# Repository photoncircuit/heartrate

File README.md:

# Heart Rate Monitoring System
Bachelors degree final project: portable heart rate monitoring system with bluetooth data transfer capability

The aim of this project is to design and construct a functional heart rate monitoring system. The device will amplify pulse measurements taken from an individual’s fingertip. The system is based on an active band pass filter which will amplify a selected signal frequency while attenuating noise and interference. Signals acquired from the fingertip sensor will be analogue and require conversion to digital. The use of an analogue to digital convertor (ADC) is employed in order for the microcontroller to process the information taken from the individual. After processing, the microcontroller will display pulse rate data on an LCD display and transmit the information wirelessly through the use of the Bluetooth communication protocol. It enables the user to move the device to any area desirable within their homes. A user can then view the transmitted data on an application, using a graphical user interface, running on their personal computers. Implementing this technology allows for users to easily monitor and log data about their personal health. The results collected from thorough testing indicate that even with precautions taken, noise and interference are still major causes of signal corruption.

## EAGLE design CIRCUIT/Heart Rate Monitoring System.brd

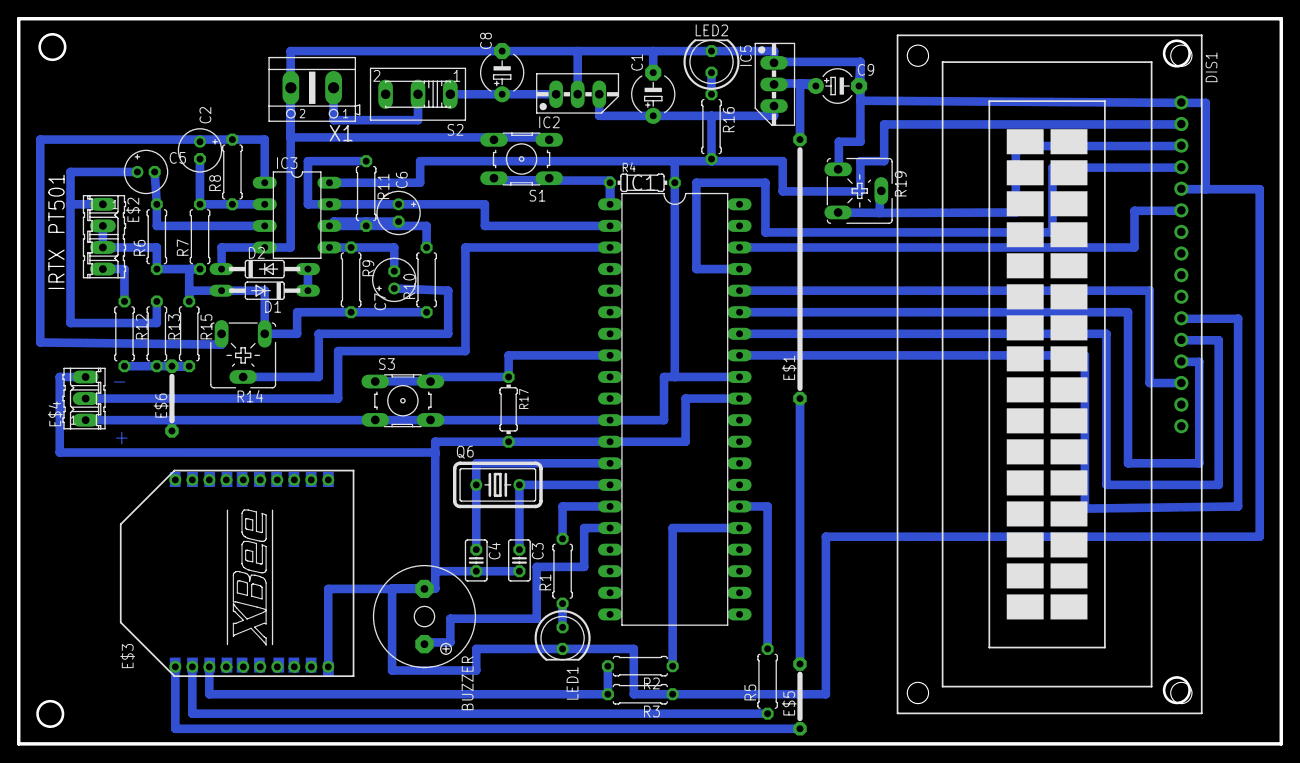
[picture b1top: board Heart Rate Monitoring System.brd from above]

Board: 2 copper layers, 148.6 x 85.3 mm, 48 parts (0 on the bottom side), 39 nets.

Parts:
BUZZER: F/QMBIII
C1, C8: 220uF; E5-5
C2, C6: 0.47uF; E2-5
C3, C4: 22p; C025-025X050
C5, C7: 10uF; E2-5
C9: 220uF; E5-4
D1, D2: 1N4148; DO35-10
DIS1: TUXGR_16X2_R2
E$1: 30
E$2: 04P
E$3: BLUEBEE; XBEE
E$4: LM35DZ; 03P
E$5, E$6: 07
IC1: PIC16F877P; DIL40
IC2: LM7805; 78MXXS
IC3: LM358N; DIL08
IC5: LM1117; 78MXXS
LED1, LED2: LED5MM
Q6: 4MHz; HC18U-V
R1, R7, R10, R16: 1K; 0207/7
R2, R5: 1.8K; 0207/7
R3: 3.3K; 0207/7
R4, R17: 1.5K; 0204/7
R6, R9, R13: 20K; 0207/7
R8, R11: 100K; 0207/7
R12: 100; 0207/7
R14, R19: 10K; CA6V
R15: 5K; 0207/7
S1, S3: B3F-10XX
S2: 255SB
X1: AK500/2

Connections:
GND: BUZZER.-, C1.-, C3.2, C4.2, C8.-, C9.-, D2.C, DIS1.1, DIS1.5, E$3.10, E$4.3, IC1.12, IC1.31, IC2.GND, IC3.4, IC5.IN, LED1.K, LED2.K, R3.1, R17.2, R19.A, S1.3, S1.4, X1.2
unnamed: C2.+, IC3.1, R8.2, R14.E
unnamed: C5.-, IC3.3, R6.2
unnamed: S2.2, X1.1
unnamed: IC1.1, R4.1, S1.1, S1.2
unnamed: C3.1, IC1.14, Q6.2
unnamed: LED1.A, R1.1
unnamed: IC1.15, R1.2
unnamed: BUZZER.+, IC1.16
unnamed: C2.-, IC3.2, R7.2, R8.1
unnamed: C7.+, R14.S
unnamed: C7.-, IC3.5, R9.1
unnamed: C6.+, IC1.2, IC3.7, R11.1
unnamed: C6.-, IC3.6, R10.2, R11.2
unnamed: C5.+, E$2.1, R13.1
unnamed: C4.1, IC1.13, Q6.1
unnamed: E$2.4, R12.1
unnamed: D1.C, D2.A
unnamed: D1.A, E$2.2, E$2.3, R6.1, R7.1, R9.2, R10.1, R14.A, R15.1
unnamed: E$3.2, R5.1
unnamed: IC1.25, R2.1
unnamed: E$3.3, R2.2, R3.2
unnamed: IC1.26, R5.2
unnamed: DIS1.11, IC1.33
unnamed: DIS1.12, IC1.34
unnamed: DIS1.13, IC1.35
unnamed: DIS1.6, IC1.38
unnamed: DIS1.3, R19.E, R19.S
unnamed: DIS1.14, IC1.36
unnamed: DIS1.4, IC1.37
S$1: E$4.2, IC1.3
S$2: C9.+, E$1.2, IC5.GND
S$3: IC1.8, R17.1, S3.1, S3.2
S$4: E$6.2, R12.2, R13.2, R15.2
S$5: E$1.1, E$5.2
S$23: LED2.A, R16.1
S$24: E$3.1, E$5.1
V+: C8.+, IC2.IN, S2.1
VCC: C1.+, DIS1.2, E$4.1, E$6.1, IC1.11, IC1.32, IC2.OUT, IC3.8, IC5.OUT, R4.2, R16.2, S3.3, S3.4
